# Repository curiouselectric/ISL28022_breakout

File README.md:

# ISL28022_breakout
This is a breakout board for the ISL28022 DC Power monitoring IC with I2C

The ISL28022 from Renesas has a datasheet available here: https://www.renesas.com/us/en/products/amplifiers-buffers/all-amplifiers/digital-power-monitors/device/ISL28022.html

It is a DC power monitoring IC, which measures current and voltage and calculates power. The data is read at either 14 or 15 bit resolution. Data can be obtained via an I2C connection.

The maximum voltage is 60V DC and the current can be up to 320mV measured across a current shunt.

This folder contains the PCB design files for a simple break out board which can be connected to a microcontroller of your choice.

It is available to buy here: https://www.curiouselectric.co.uk/

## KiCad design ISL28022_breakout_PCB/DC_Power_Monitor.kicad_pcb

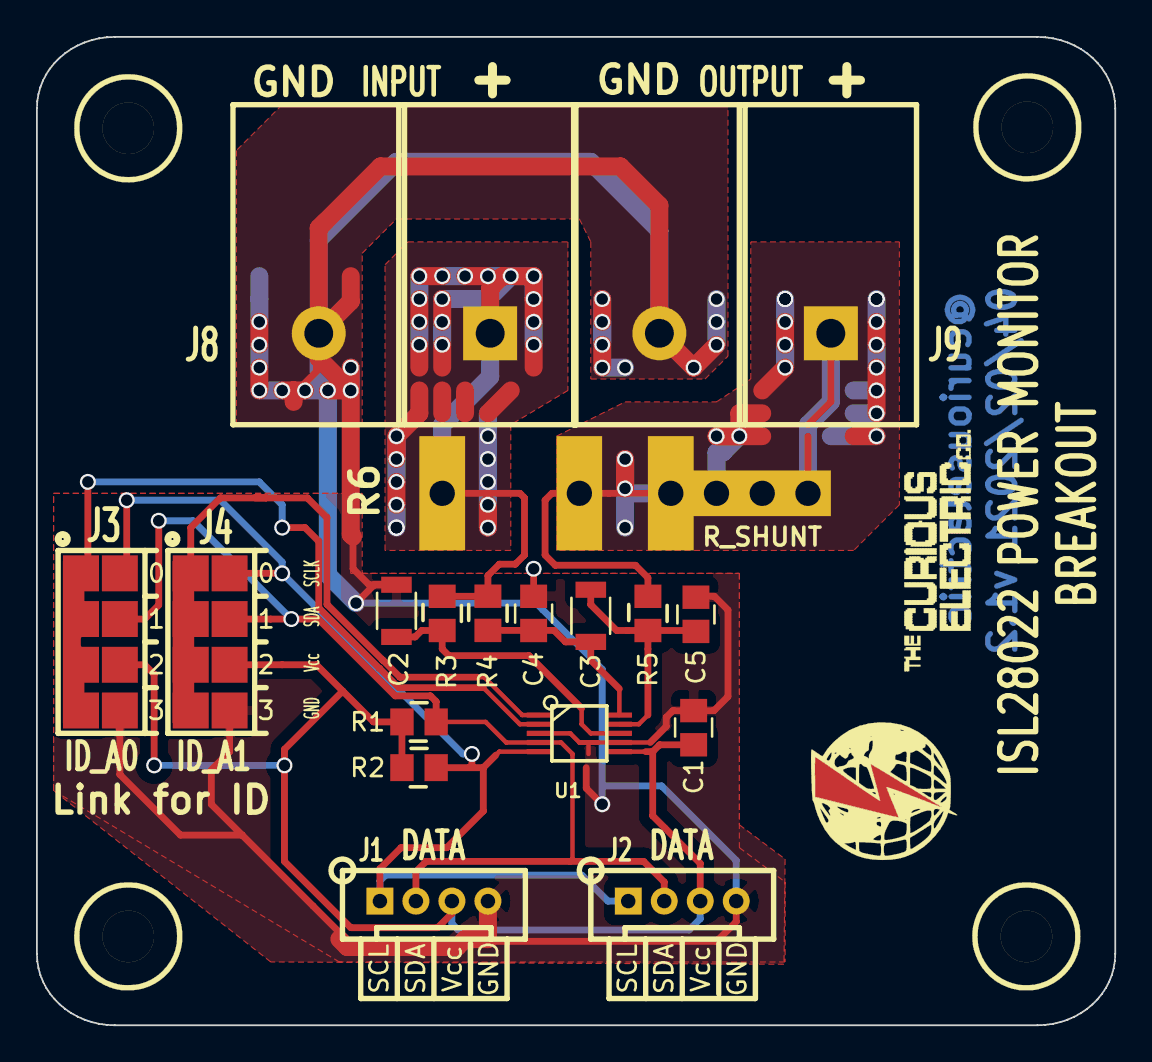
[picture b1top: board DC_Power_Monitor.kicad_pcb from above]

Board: 2 copper layers, 59.9 x 54.9 mm, 21 parts (1 on the bottom side), 11 nets.

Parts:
C1: 100n; SM_C_0805
C2: 2.2u; SM_R_1206
C3: 1u; SM_R_1206
C4, C5: 10n; SM_C_0805
J1, J2: DATA; SIL-4_Grove_Labelled_Correct
J3: ID_A0; SM_SOLDER_ID_4_WAY
J4: ID_A1; SM_SOLDER_ID_4_WAY
J5: PCB; PCB_60x55_outline
J6: LOGO1; 2019_011_16_CuriousElectricCompany_Logo_Round_Logo_No_words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
J7: LOGO2; TCEC_Words_13mm
J8: INPUT; TH_SIL-2_screw_terminal_32A_LARGE
J9: OUTPUT; TH_SIL-2_screw_terminal_32A_LARGE
R1, R2: 4.7k; SM0805
R3, R4, R5: 470R; SM0805
R6: R_SHUNT; Rshunt_universal
U1: ISL28022; MSOP10-0.5

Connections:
/Ishn: J9.1, R5.2, R6.2
/Ishp: J8.1, R3.2, R4.2, R6.1
/SCLK: J1.1, J2.1, J3.2, J4.2, R2.1, U1.5
/SDA: J1.2, J2.2, J3.3, J4.3, R1.1, U1.4
/Vcc: C1.2, J1.3, J2.3, J3.4, J4.4, R1.2, R2.2, U1.6
GND: C1.1, C2.2, C4.2, C5.2, J1.4, J2.4, J3.5, J4.5, J8.2, J9.2, U1.3, U1.7
unnamed: C2.1, R3.1, U1.8
unnamed: C3.1, C4.1, R4.1, U1.10
unnamed: C3.2, C5.1, R5.1, U1.9
unnamed: J3.1, U1.2
unnamed: J4.1, U1.1

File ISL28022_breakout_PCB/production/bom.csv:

Designator,Footprint,Quantity,Value,LCSC Part #
C1,SM_C_0805,1,100n,
C2,SM_R_1206,1,2.2u,
C3,SM_R_1206,1,1u,
"C4, C5",SM_C_0805,2,10n,
"J1, J2",SIL-4_Grove_Labelled_Correct,2,DATA,
J3,SM_SOLDER_ID_4_WAY,1,ID_A0,
J4,SM_SOLDER_ID_4_WAY,1,ID_A1,
J5,PCB_60x55_outline,1,PCB,
J6,2019_011_16_CuriousElectricCompany_Logo_Round_Logo_No_words_KiCAD_10mm_PCBLogo,1,LOGO1,
J7,TCEC_Words_13mm,1,LOGO2,
J8,TH_SIL-2_screw_terminal_32A_LARGE,1,INPUT,
J9,TH_SIL-2_screw_terminal_32A_LARGE,1,OUTPUT,
"R1, R2",SM0805,2,4.7k,
"R3, R4, R5",SM0805,3,470R,
R6,Rshunt_universal,1,R_SHUNT,
U1,MSOP10-0.5,1,ISL28022,

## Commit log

2020-11-21 Update with PCB added
2021-06-03 updated PCB and instructions
2021-06-03 updated firmware example
2021-06-07 updated instructions
2021-06-11 added pdf instructions
2024-07-30 Updated for higher voltage
    Changed int16_t to uint16_t to deal with higher numbers.
